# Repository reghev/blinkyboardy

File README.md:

This is one of my projects for stasis and its pretty cool

Its a dinosaur that lights up alot and has an eye made of a capacitor, it holds no use other than being shelf fodder 

I think that this was a good way to get familiar with kicad again because i haven't used it in a solid year and sum and overall was really fun, I think that its better off being something funny like desk fodder because i doubt ill actually have any pcb that ill use for productivity or for being something more than a gag

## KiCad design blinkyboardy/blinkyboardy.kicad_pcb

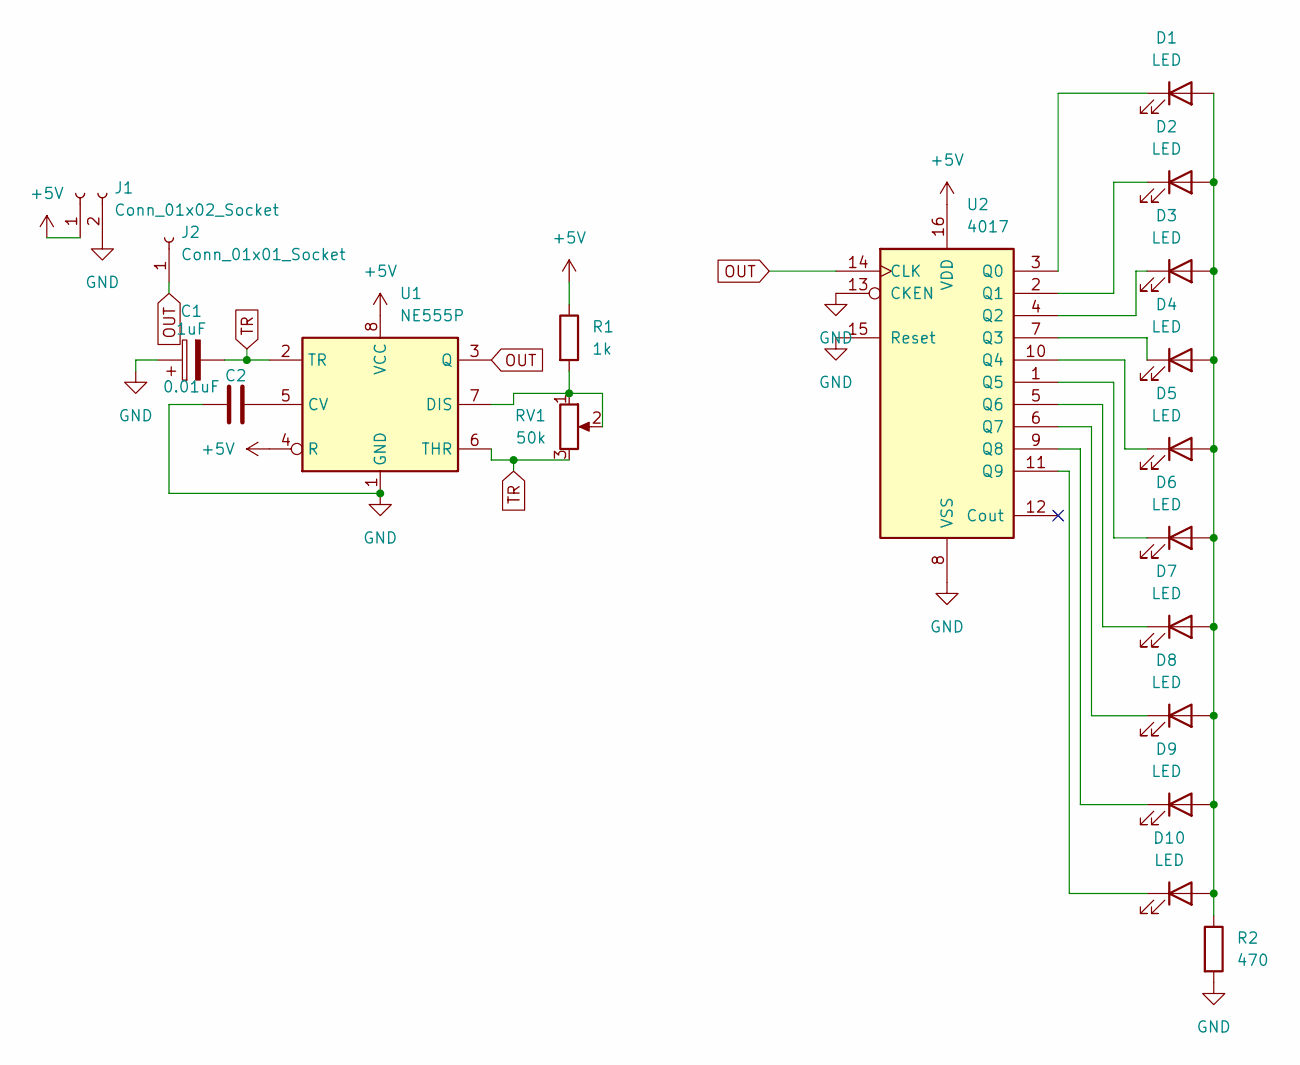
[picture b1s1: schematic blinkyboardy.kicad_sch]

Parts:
C1: 1uF; CP_Radial_D5.0mm_P2.00mm
C2: 0.01uF; C_Disc_D7.5mm_W2.5mm_P5.00mm
D1, D2, D3, D4, D5, D6, D7, D8, D9, D10: LED; LED_D3.0mm
J1: Conn_01x02_Socket; PinSocket_1x02_P2.54mm_Vertical
J2: Conn_01x01_Socket; PinSocket_1x01_P2.54mm_Vertical
R1: 1k; R_Axial_DIN0207_L6.3mm_D2.5mm_P7.62mm_Horizontal
R2: 470; R_Axial_DIN0207_L6.3mm_D2.5mm_P7.62mm_Horizontal
RV1: 50k; Potentiometer_Vishay_T93YA_Vertical
U1: NE555P; DIP-8_W7.62mm
U2: 4017; N16

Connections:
+5V: J1.1, R1.1, U1.4 (R), U1.8 (VCC), U2.16 (VDD)
GND: C1.1, C2.1, J1.2, R2.2, U1.1 (GND), U2.8 (VSS), U2.13 (CKEN), U2.15 (Reset)
unnamed: D1.2 (A), D2.2 (A), D3.2 (A), D4.2 (A), D5.2 (A), D6.2 (A), D7.2 (A), D8.2 (A), D9.2 (A), D10.2 (A), R2.1
unnamed: D1.1 (K), U2.3 (Q0)
unnamed: D2.1 (K), U2.2 (Q1)
unnamed: D3.1 (K), U2.4 (Q2)
unnamed: D4.1 (K), U2.7 (Q3)
unnamed: D5.1 (K), U2.10 (Q4)
unnamed: D6.1 (K), U2.1 (Q5)
unnamed: D7.1 (K), U2.5 (Q6)
unnamed: D8.1 (K), U2.6 (Q7)
unnamed: D9.1 (K), U2.9 (Q8)
unnamed: D10.1 (K), U2.11 (Q9)
unnamed: C2.2, U1.5 (CV)
unnamed: R1.2, RV1.1, RV1.2, U1.7 (DIS)
OUT: J2.1, U1.3 (Q), U2.14 (CLK)
TR: C1.2, RV1.3, U1.2 (TR), U1.6 (THR)

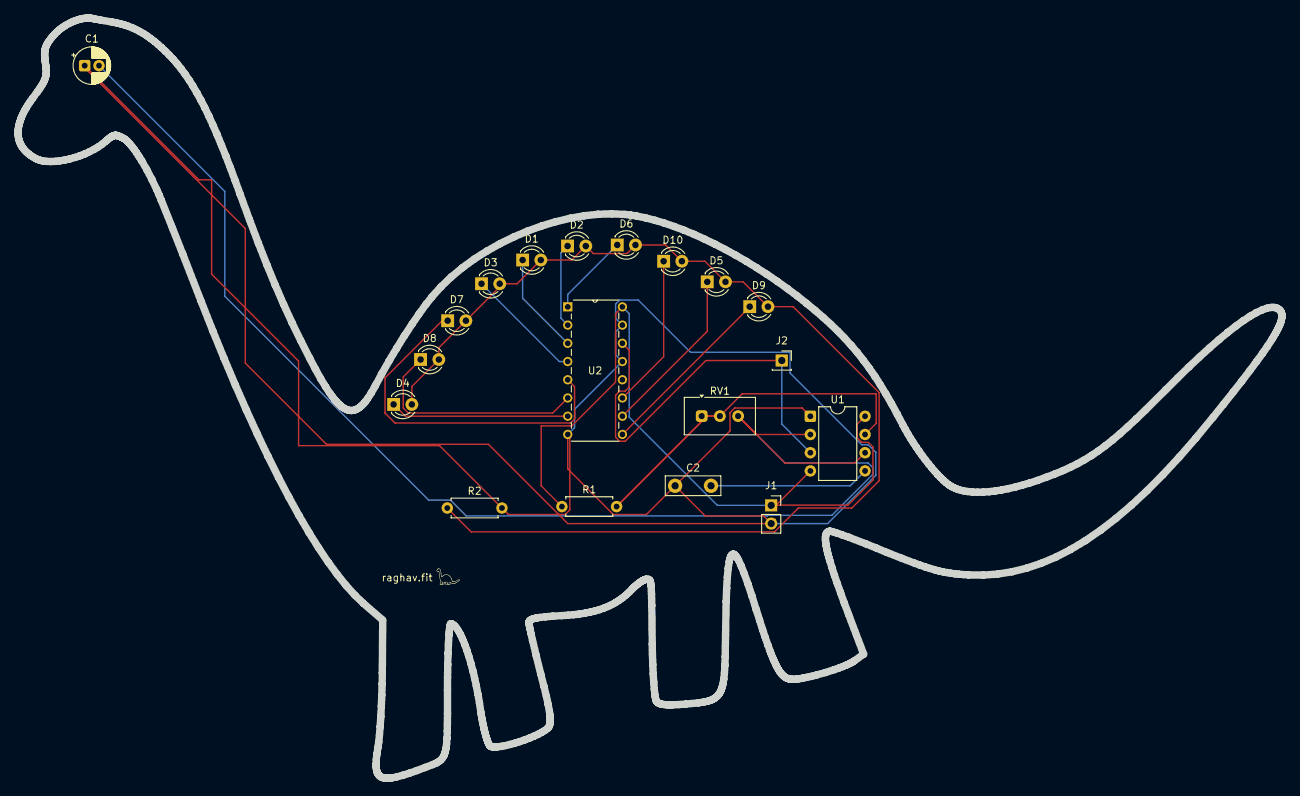
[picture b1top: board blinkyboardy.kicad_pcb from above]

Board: 2 copper layers, 176.2 x 106.0 mm, 19 parts (0 on the bottom side), 17 nets.

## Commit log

2026-05-02 README
2026-05-03 Enhance project description in README
    Added a description of the dinosaur project.
2026-05-10 Enhance project description in README
    Added additional details about the project and images.
2026-05-13 Revise project description and personal insights
    Expanded on the project's purpose and personal reflections.
